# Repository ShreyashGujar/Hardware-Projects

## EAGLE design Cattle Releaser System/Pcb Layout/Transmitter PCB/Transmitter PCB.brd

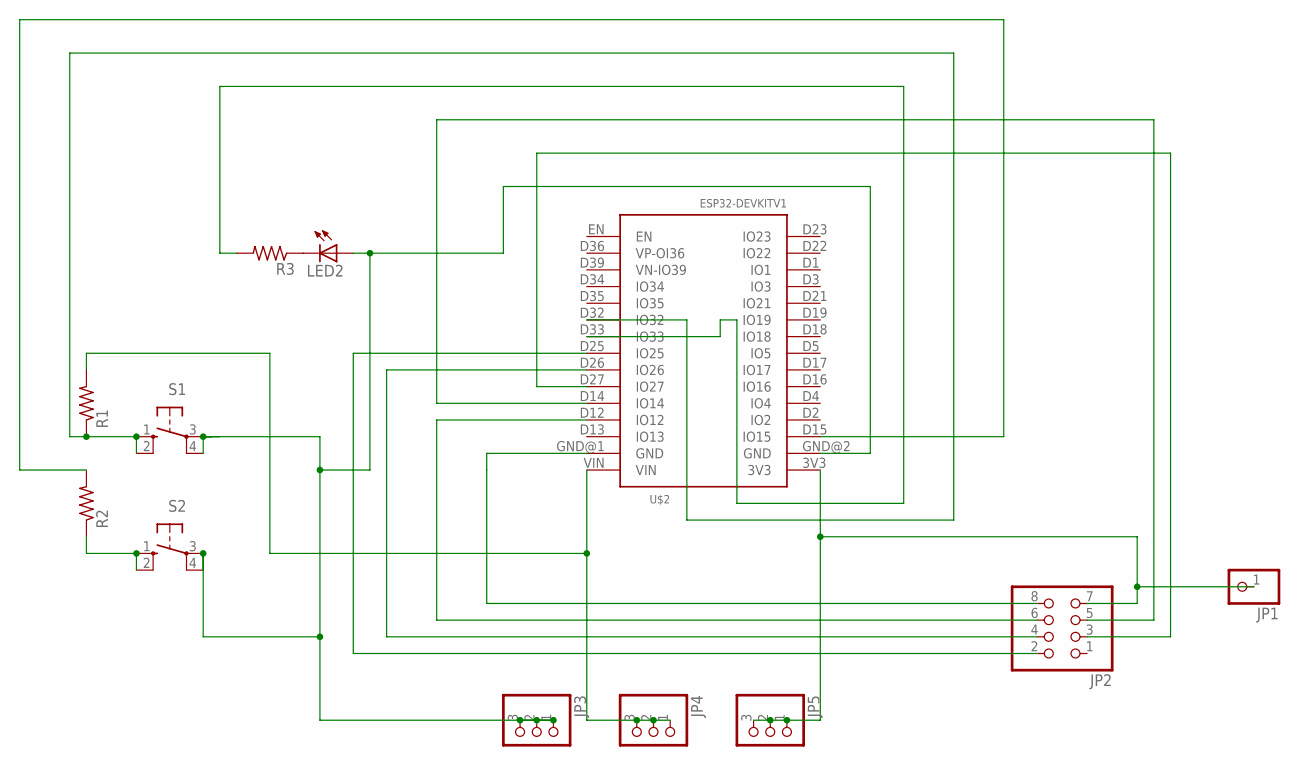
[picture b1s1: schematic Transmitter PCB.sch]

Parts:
JP1: PINHD-1X1; 1X01
JP2: PINHD-2X4; 2X04
JP3, JP4, JP5: PINHD-1X3; 1X03
LED2: LED5MM
R1, R2, R3: R-US_0207/7; 0207/7
S1, S2: 10-XX; B3F-10XX
U$2: ESP32DEVKITV1; ESP32-DEVKITV1

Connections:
GND: JP2.8, U$2.GND@1 (GND)
LED2: R3.2, U$2.D33 (IO33)
unnamed: R2.1, S2.1 (S), S2.2 (S1)
unnamed: JP3.1, JP3.2, JP3.3, LED2.A, S1.3, S1.4 (P1), S2.3, S2.4 (P1), U$2.GND@2 (GND)
unnamed: JP2.4, U$2.D26 (IO26)
unnamed: JP2.2, U$2.D25 (IO25)
unnamed: JP1.1, JP2.7, JP5.1, JP5.2, JP5.3, U$2.3V3
unnamed: JP2.3, U$2.D27 (IO27)
unnamed: LED2.K (C), R3.1
unnamed: JP2.6, U$2.D12 (IO12)
unnamed: JP2.5, U$2.D14 (IO14)
unnamed: R2.2, U$2.D15 (IO15)
RST: R1.1, S1.1 (S), S1.2 (S1), U$2.D32 (IO32)
VCC: JP4.1, JP4.2, JP4.3, R1.2, U$2.VIN

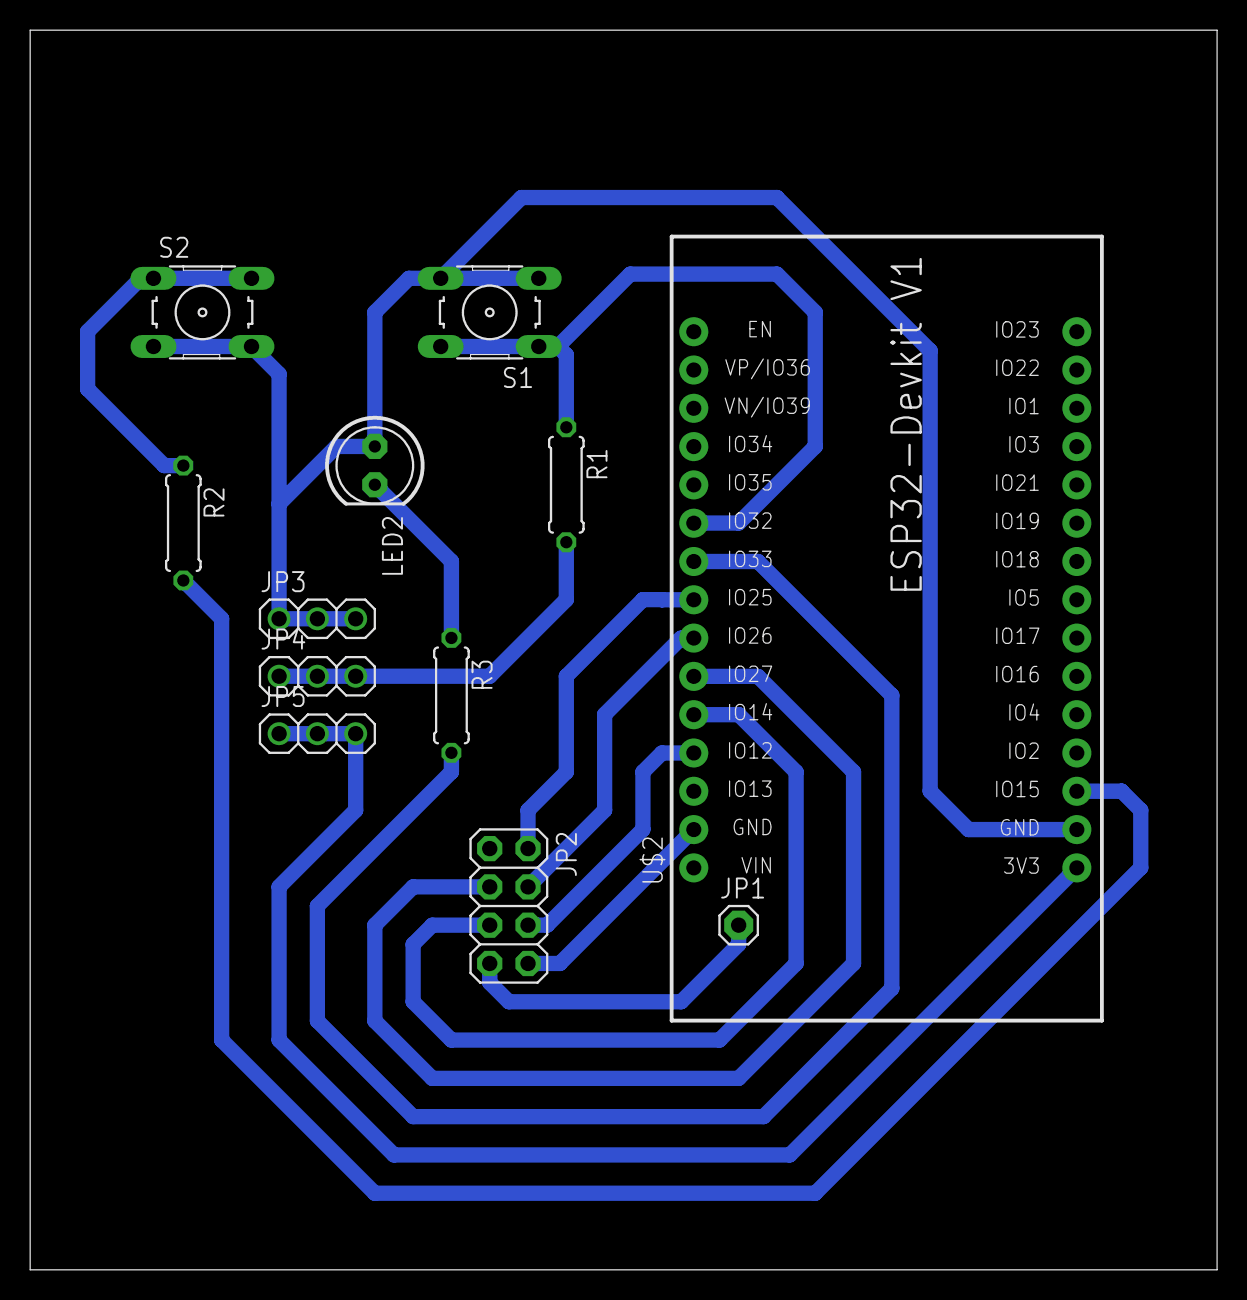
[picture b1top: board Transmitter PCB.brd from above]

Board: 2 copper layers, 78.7 x 82.2 mm, 12 parts (0 on the bottom side), 14 nets.

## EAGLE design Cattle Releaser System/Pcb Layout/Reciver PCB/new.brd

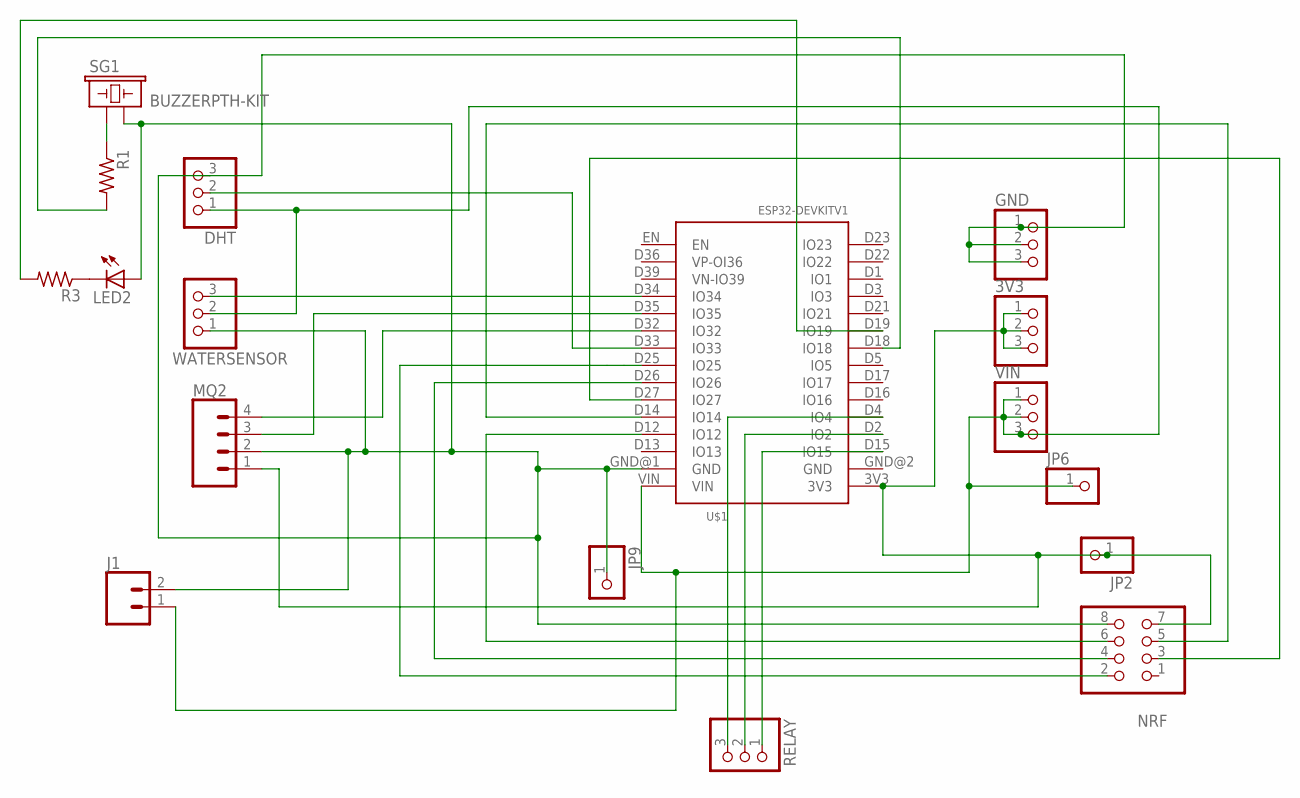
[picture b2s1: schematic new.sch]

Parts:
3V3: PINHD-1X3; 1X03
DHT: PINHD-1X3; 1X03
GND: PINHD-1X3; 1X03
J1: CONN_02; 1X02
JP2, JP6, JP9: PINHD-1X1; 1X01
LED2: LED5MM
MQ2: CONN_04PTH; 1X04
NRF: PINHD-2X4; 2X04
R1, R3: R-US_0207/7; 0207/7
RELAY: PINHD-1X3; 1X03
SG1: BUZZERPTH-KIT; BUZZER-12MM-KIT
U$1: ESP32DEVKITV1; ESP32-DEVKITV1
VIN: PINHD-1X3; 1X03
WATERSENSOR: PINHD-1X3; 1X03

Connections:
unnamed: R1.1, SG1.+ (1)
unnamed: R1.2, U$1.D18 (IO18)
unnamed: NRF.4, U$1.D26 (IO26)
unnamed: NRF.2, U$1.D25 (IO25)
unnamed: DHT.3, GND.1, GND.2, GND.3, J1.2, JP9.1, LED2.A, MQ2.2, NRF.8, SG1.- (2), U$1.GND@1 (GND), WATERSENSOR.1
unnamed: R3.2, U$1.D19 (IO19)
unnamed: NRF.3, U$1.D27 (IO27)
unnamed: LED2.K (C), R3.1
unnamed: NRF.6, U$1.D12 (IO12)
unnamed: NRF.5, U$1.D14 (IO14)
unnamed: DHT.2, U$1.D33 (IO33)
unnamed: DHT.1, J1.1, JP6.1, U$1.VIN, VIN.1, VIN.2, VIN.3, WATERSENSOR.2
unnamed: U$1.D34 (IO34), WATERSENSOR.3
unnamed: RELAY.3, U$1.D4 (IO4)
unnamed: RELAY.2, U$1.D2 (IO2)
unnamed: MQ2.4, U$1.D32 (IO32)
unnamed: MQ2.3, U$1.D35 (IO35)
unnamed: RELAY.1, U$1.D15 (IO15)
unnamed: 3V3.1, 3V3.2, 3V3.3, JP2.1, MQ2.1, NRF.7, U$1.3V3

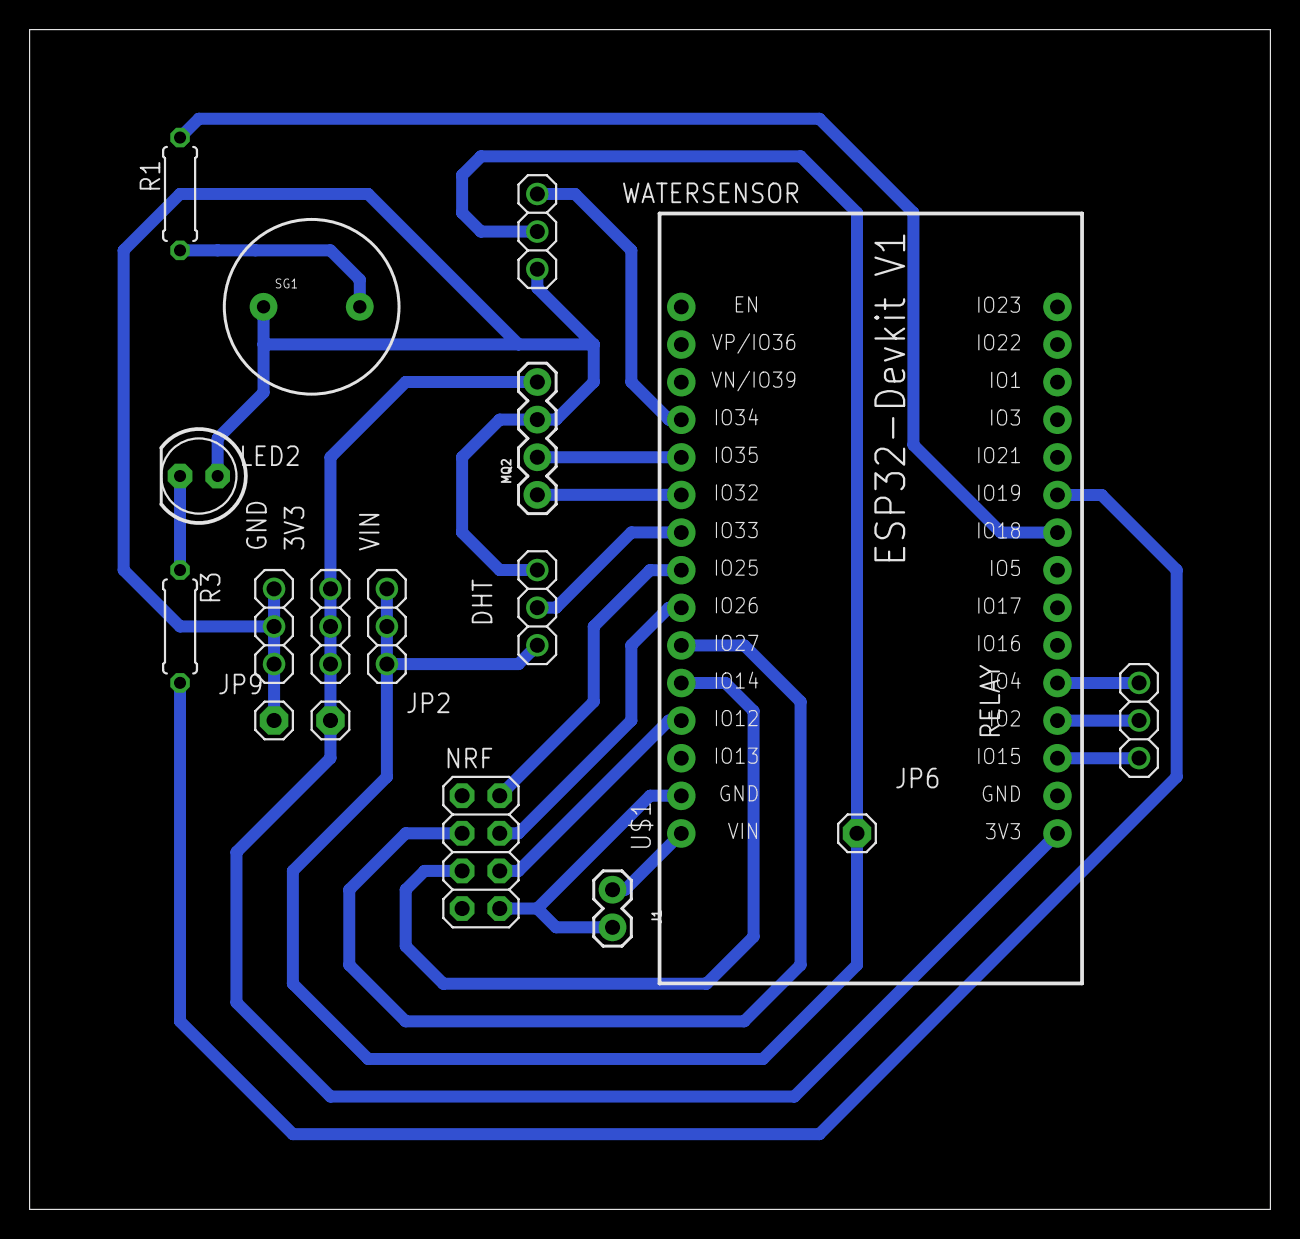
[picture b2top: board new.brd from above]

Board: 2 copper layers, 83.8 x 79.7 mm, 17 parts (0 on the bottom side), 19 nets.

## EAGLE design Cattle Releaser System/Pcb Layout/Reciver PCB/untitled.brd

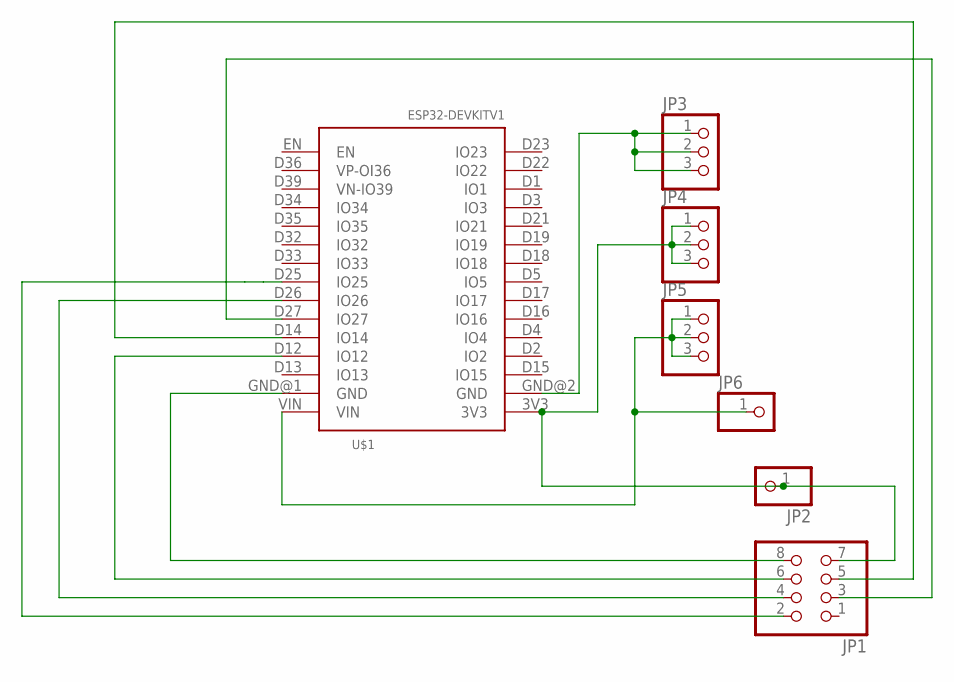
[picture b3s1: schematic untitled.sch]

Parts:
JP1: PINHD-2X4; 2X04
JP2, JP6: PINHD-1X1; 1X01
JP3, JP4, JP5: PINHD-1X3; 1X03
U$1: ESP32DEVKITV1; ESP32-DEVKITV1

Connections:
unnamed: JP1.8, U$1.GND@1 (GND)
unnamed: JP3.1, JP3.2, JP3.3, U$1.GND@2 (GND)
unnamed: JP1.4, U$1.D26 (IO26)
unnamed: JP1.2, U$1.D25 (IO25)
unnamed: JP1.7, JP2.1, JP4.1, JP4.2, JP4.3, U$1.3V3
unnamed: JP1.3, U$1.D27 (IO27)
unnamed: JP5.1, JP5.2, JP5.3, JP6.1, U$1.VIN
unnamed: JP1.6, U$1.D12 (IO12)
unnamed: JP1.5, U$1.D14 (IO14)

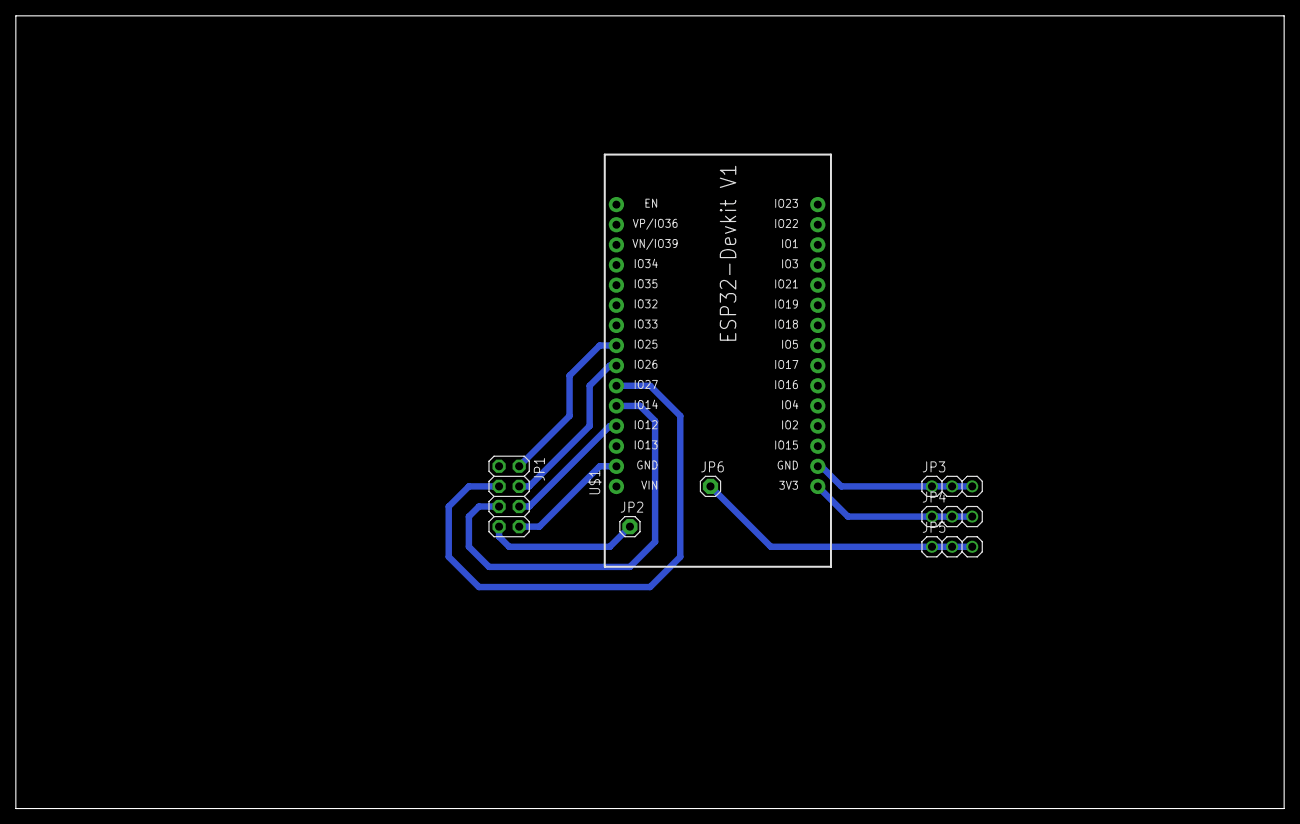
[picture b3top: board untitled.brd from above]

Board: 2 copper layers, 160.0 x 100.0 mm, 7 parts (0 on the bottom side), 9 nets.

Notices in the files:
parts and their libraries:
SparkFun-Connectors: Licensing: Creative Commons ShareAlike 4.0 International - https://creativecommons.org/licenses/by-sa/4.0
